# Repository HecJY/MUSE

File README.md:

# MUSE
MUSE is a project for Purdue University course of ECE362. It is a electric piano keyboard embedded in a STM32f051.

## Main Feature
 - The electric piano has two ocatives, and has 15 white keys with 10 black keys in total.
 - The electric piano has chord, which means you can put down different buttons at the same time.
 - The electric piano...polyphonic wave...

## Note
 - The body case can be done by different means; for instance, we used a lazor cutter to cut a piece of wood board for making a case.
 - The keyboard was 3D-printed, and it is helpful to check out the OKAY 2 Synth keyboard for reference.
 - The circuit design includes an Eagle version and an Altium version; the Altium version is a more sophisticated version in terms of its design.
 
## Build & Test
 - This project is developed on System Workbench for STM32.
 - To test the project, first build within Workbench, and then hit "Run".
 - A builded breadboard circuit is needed for testing; users can refer to dianlutu.sch for circuit building.

## Contributors
Jiaxing Yang (HecJY), Yining Huang (hyncharlotte), Litao Xu, Haotian Zheng

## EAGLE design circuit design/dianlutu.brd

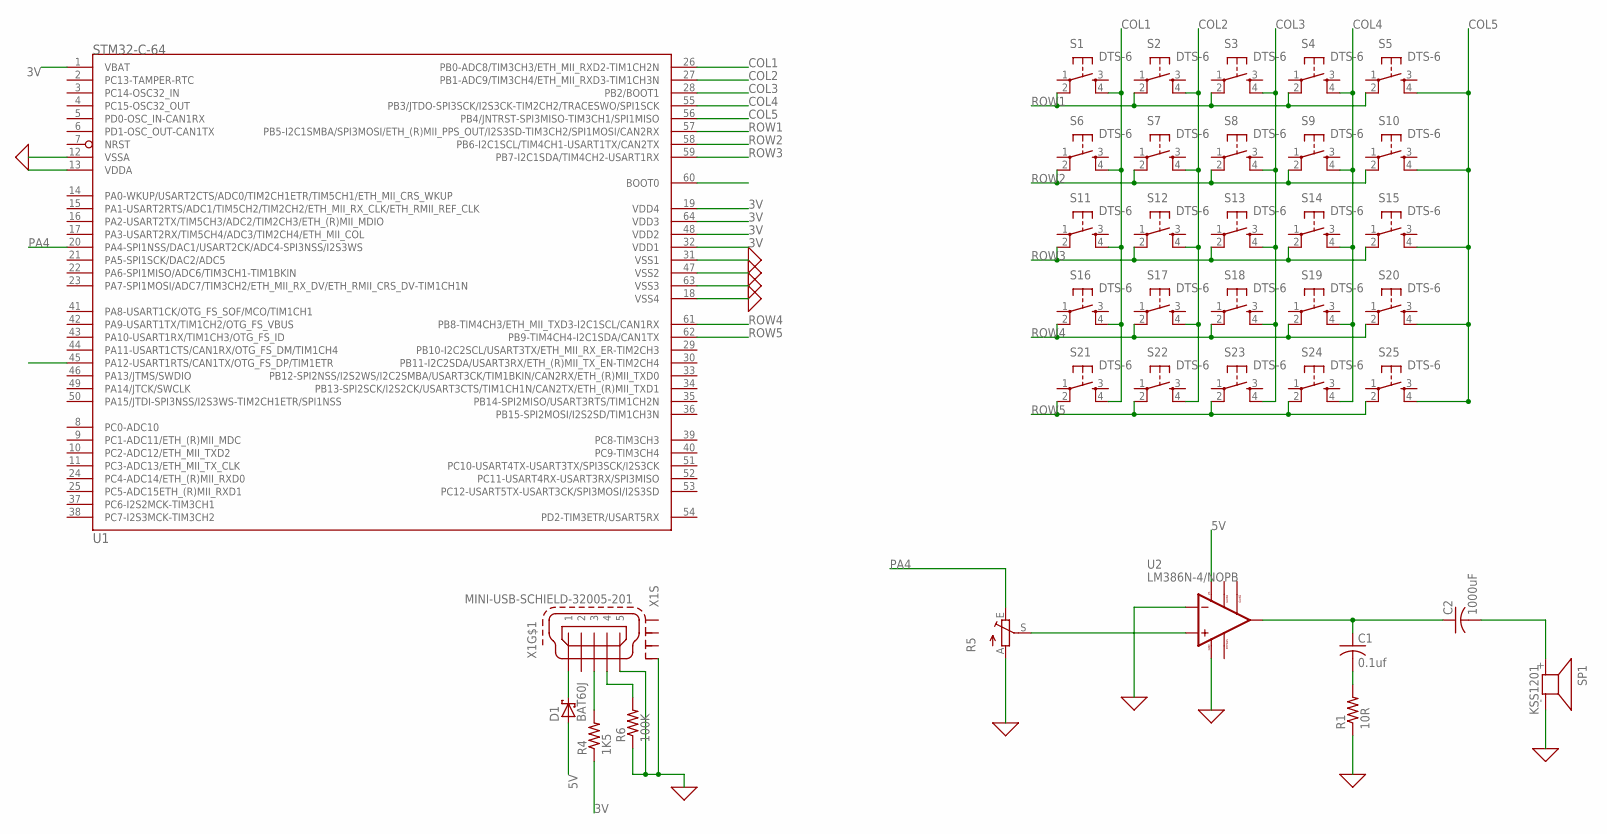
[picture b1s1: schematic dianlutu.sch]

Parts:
C1: 0.1uf; C0805
C2: 1000uF; C0805
D1: BAT60J; SOD323_ST
R1: 10R; R0805
R4: 1K5; R0805
R5: TRIM_EU-S63S; S63S
R6: 100K; M0805
S1, S2, S3, S4, S5, S6, S7, S8, S9, S10, S11, S12, S13, S14, S15, S16, S17, S18, S19, S20, S21, S22, S23, S24, S25: DTS-6
SP1: KSS1201
U1: STM32-C-64; LQFP64
U2: LM386N-4/NOPB; DIP794W45P254L1016H508Q8
X1: MINI-USB-SCHIELD-32005-201; 32005-201

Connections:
0: R1.1, R5.A, R6.1, SP1.- (2), U1.12 (VSSA), U1.18 (VSS4), U1.31 (VSS1), U1.47 (VSS2), U1.63 (VSS3), U2.2 (-INPUT), U2.4 (GND), X1.5, X1.M1 (S1)
3V: R4.1, U1.1 (VBAT), U1.19 (VDD4), U1.32 (VDD1), U1.48 (VDD2), U1.64 (VDD3)
5V: D1.A, U2.6 (VS)
COL1: S1.4, S6.4, S11.4, S16.4, S21.4, U1.26 (PB0-ADC8/TIM3CH3/ETH_MII_RXD2-TIM1CH2N)
COL2: S2.4, S7.4, S12.4, S17.4, S22.4, U1.27 (PB1-ADC9/TIM3CH4/ETH_MII_RXD3-TIM1CH3N)
COL3: S3.4, S8.4, S13.4, S18.4, S23.4, U1.28 (PB2/BOOT1)
COL4: S4.4, S9.4, S14.4, S19.4, S24.4, U1.55 (PB3/JTDO-SPI3SCK/I2S3CK-TIM2CH2/TRACESW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)
COL5: S5.4, S10.4, S15.4, S20.4, S25.4, U1.56 (PB4/JNTRST-SPI3MISO-TIM3CH1/SPI1MISO)
unnamed: D1.C, X1.1
unnamed: C2.2, SP1.+ (1)
unnamed: R6.2, X1.4
unnamed: C1.2, R1.2
unnamed: R5.S, U2.3 (+INPUT)
unnamed: C1.1, C2.1, U2.5 (VOUT)
PA4: R5.E, U1.20 (PA4-SPI1NSS/DAC1/USART2CK/ADC4-SPI3NSS/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)
ROW1: S1.2, S2.2, S3.2, S4.2, S5.2, U1.57 (PB5-I2C1SMBA/SPI3MOSI/ETH_(R)MII_PPS_OU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)
ROW2: S6.2, S7.2, S8.2, S9.2, S10.2, U1.58 (PB6-I2C1SCL/TIM4CH1-USART1TX/CAN2TX)
ROW3: S11.2, S12.2, S13.2, S14.2, S15.2, U1.59 (PB7-I2C1SDA/TIM4CH2-USART1RX)
ROW4: S16.2, S17.2, S18.2, S19.2, S20.2, U1.61 (PB8-TIM4CH3/ETH_MII_TXD3-I2C1SCL/CAN1RX)
ROW5: S21.2, S22.2, S23.2, S24.2, S25.2, U1.62 (PB9-TIM4CH4-I2C1SDA/CAN1TX)
USB_DP: R4.2, X1.3
VDDA: U1.13 (VDDA)

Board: 2 copper layers, 36 parts (0 on the bottom side), 21 nets, no tracks yet.

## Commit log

2019-04-15 Add files via upload
    Add the delay function, update on the gpio
2019-04-15 Add files via upload
    wave generate function
2019-04-15 finished debugging the wave generation function
2019-04-16 finish composing the wavetable
2019-04-16 generate major C waveform
2019-04-16 Add files via upload
    voice function finished
2019-04-16 Add files via upload
    main update and btn initialized
2019-04-16 adding pcb design
2019-04-17 update progress
2019-04-17 pcb design
2019-04-18 update files
2019-04-18 jms code update
2019-04-18 update circuit
2019-04-19 mini
2019-04-19 reorganize jms code
2019-08-17 Altium circuit design
2019-08-18 Update README.md
    need more update
    coming soon
